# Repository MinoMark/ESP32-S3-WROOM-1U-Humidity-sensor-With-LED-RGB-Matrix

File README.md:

# ESP32-S3-WROOM-1U-Humidity-sensor-With-LED-RGB-Matrix
The project I am building is an ESP32-S3 WROOM-1U humidity sensor with an LED RGB matrix. This project is a really cool one. The ESP will control and read the data from the sensor and output certain colours, patterns, or make the lights move based on the temperature, humidity, and air quality.

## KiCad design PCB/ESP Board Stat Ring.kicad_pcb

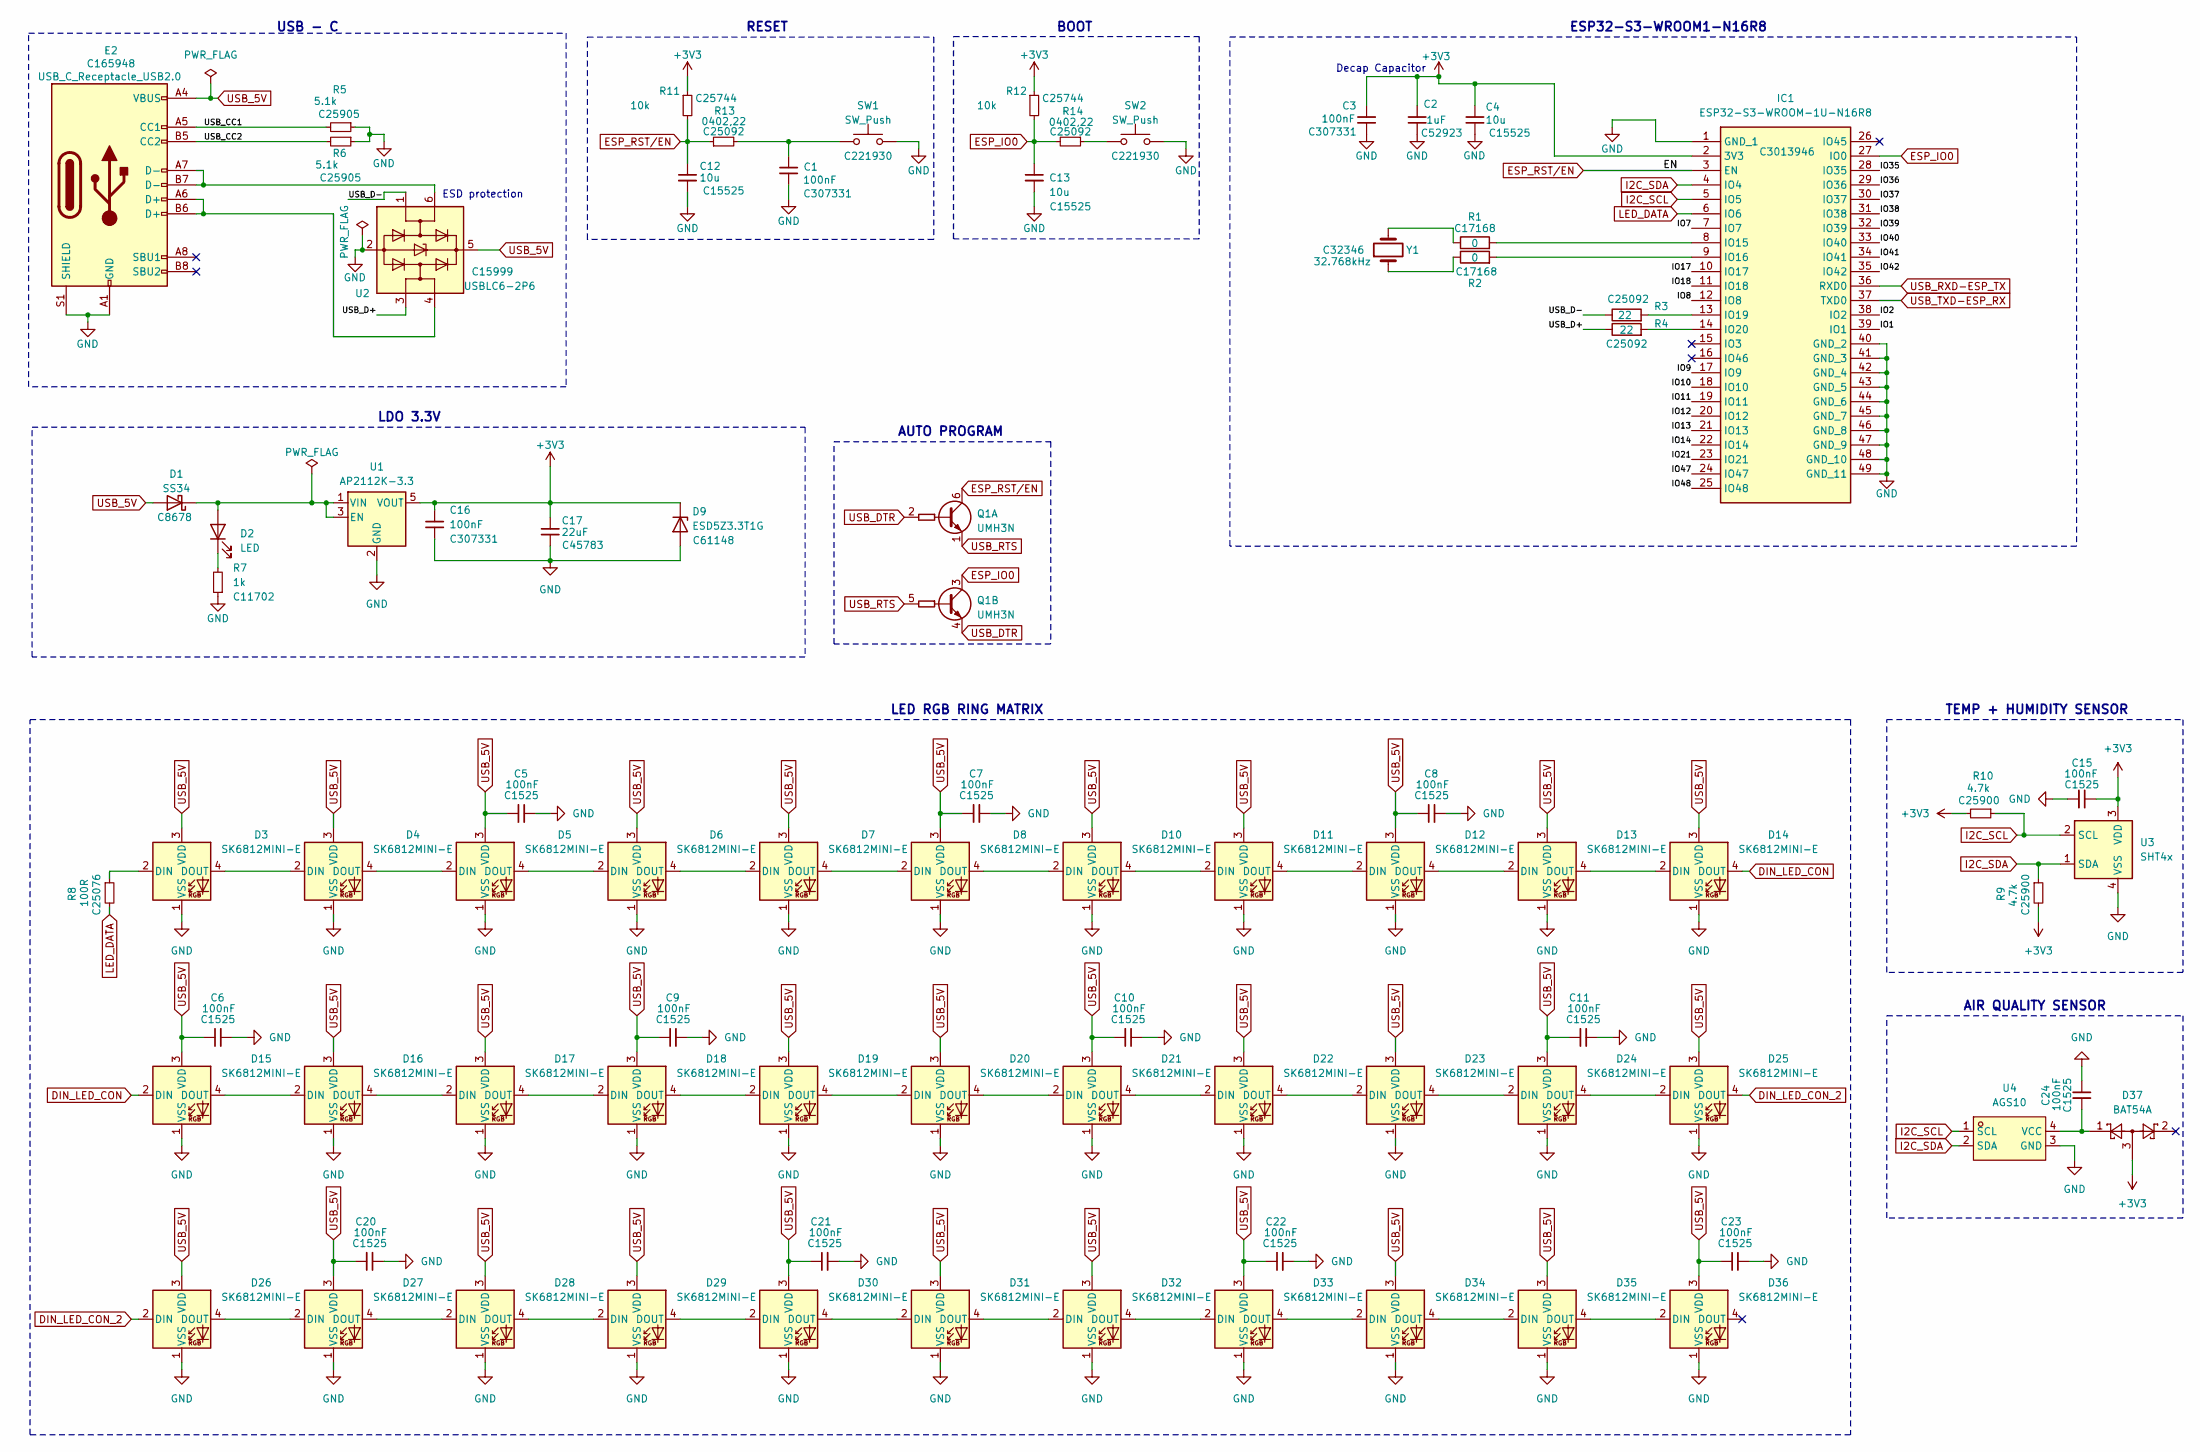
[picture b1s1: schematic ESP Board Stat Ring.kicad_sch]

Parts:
C1, C3, C16: 100nF; C_0402_1005Metric; MFGPN CL05B104KB54PNC; LCSC C307331
C2: 1uF; C_0402_1005Metric; MFGPN CL05A105KA5NQNC; LCSC C52923
C4: 10u; C_0402_1005Metric; MFGPN CL05B104KB54PNC; LCSC C15525
C5, C6, C7, C8, C9, C10, C11, C15, C20, C21, C22, C23, C24: 100nF; C_0402_1005Metric; MFGPN CL05B104KB54PNC; LCSC C1525
C12, C13: 10u; C_0402_1005Metric; MPN CL05A106MQ5NUNC; LCSC C15525
C17: 22uF; C_0805_2012Metric; MFGPN CL21A226MAQNNNE; LCSC C45783
D1: SS34; D_SMA; MPN SS34; LCSC C8678
D2: LED; LED_0603_1608Metric; MPN 19-217/GHC-YR1S2/3T; LCSC C72043
D3, D4, D5, D6, D7, D8, D10, D11, D12, D13, D14, D15, D16, D17, D18, D19, D20, D21, D22, D23, D24, D25, D26, D27, D28, D29, D30, D31, D32, D33, D34, D35, D36: SK6812MINI-E; LED_SK6812MINI-E_3.2x2.8mm_P1.5mm_ReverseMount; MPN SK6812MINI-E; LCSC C5149201
D9: ESD5Z3.3T1G; D_SOD-523; MPN ESD5Z3.3T1G; LCSC C61148
D37: BAT54A; SOT-23; MPN BAT54A; LCSC C181199
E2: USB_C_Receptacle_USB2.0; USB_C_Receptacle_HRO_TYPE-C-31-M-12; MPN TYPE-C-31-M-12; LCSC C165948
IC1: ESP32-S3-WROOM-1U-N16R8; ESP32-S3-WROOM-1U; Mouser Part Number 356-ESP32S3WM1UN16R8
Q1: UMH3N; SOT-363_SC-70-6; MPN UMH3N; LCSC C62892
R1, R2: 0; C_0402_1005Metric; MPN 0402WGF0000TCE; LCSC C17168
R3, R4: 22; C_0402_1005Metric; MPN 0402WGF220JTCE; LCSC C25092
R5, R6: 5.1k; R_0402_1005Metric; MFGPN 0402WGF5101TCE; LCSC C25905
R7: 1k; R_0402_1005Metric; MFGPN 0402WGF1002TCE; LCSC C11702
R8: 100R; R_0402_1005Metric; MFGPN 0402WGF5101TCE; LCSC C25076
R9, R10: 4.7k; R_0402_1005Metric; MFGPN 0402WGF5101TCE; LCSC C25900
R11, R12: 10k; R_0402_1005Metric; MFGPN 0402WGF1002TCE; LCSC C25744
R13, R14: 0402,22; R_0402_1005Metric; MFGPN 0402WGF220JTCE; LCSC C25092
SW1, SW2: SW_Push; SW_SPST_CK_RS282G05A3; MPN RS-282G05A3-SMRT; LCSC C221930
U1: AP2112K-3.3; SOT-23-5; MPN AP2112K-3.3TRG1; LCSC C51118
U2: USBLC6-2P6; SOT-666; MPN USBLC6-2P6; LCSC C15999
U3: SHT4x; Sensirion_DFN-4_1.5x1.5mm_P0.8mm_SHT4x_NoCentralPad; MPN SHT40-AD1F-R2; LCSC C54823945
U4: AGS10; SENSOR-SMD_AGS10; MPN AGS10; LCSC Part C3012632
Y1: 32.768kHz; Crystal_SMD_3215-2Pin_3.2x1.5mm; MPN 32.768kHz SMD3215; LCSC C32346

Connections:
+3V3: C2.1, C3.1, C4.1, C15.1, C16.1, C17.1, D9.1 (K), D37.3, IC1.2 (3V3), R9.2, R10.2, R11.1, R12.1, U1.5 (VOUT), U3.3 (VDD)
/IO1: IC1.39 (IO1)
/IO2: IC1.38 (IO2)
/IO7: IC1.7 (IO7)
/IO8: IC1.12 (IO8)
/IO9: IC1.17 (IO9)
/IO10: IC1.18 (IO10)
/IO11: IC1.19 (IO11)
/IO12: IC1.20 (IO12)
/IO13: IC1.21 (IO13)
/IO14: IC1.22 (IO14)
/IO17: IC1.10 (IO17)
/IO18: IC1.11 (IO18)
/IO21: IC1.23 (IO21)
/IO35: IC1.28 (IO35)
/IO36: IC1.29 (IO36)
/IO37: IC1.30 (IO37)
/IO38: IC1.31 (IO38)
/IO39: IC1.32 (IO39)
/IO40: IC1.33 (IO40)
/IO41: IC1.34 (IO41)
/IO42: IC1.35 (IO42)
/IO47: IC1.24 (IO47)
/IO48: IC1.25 (IO48)
/USB_CC1: E2.A5 (CC1), R5.2
/USB_CC2: E2.B5 (CC2), R6.2
/USB_D+: R4.1, U2.3 (I/O2)
/USB_D-: R3.1, U2.1 (I/O1)
DIN_LED_CON: D14.4 (DOUT), D15.2 (DIN)
DIN_LED_CON_2: D25.4 (DOUT), D26.2 (DIN)
ESP_IO0: C13.1, IC1.27 (IO0), Q1.3 (C2), R12.2, R14.2
ESP_RST/EN: C12.1, IC1.3 (EN), Q1.6 (C1), R11.2, R13.1
GND: C1.2, C2.2, C3.2, C4.2, C5.2, C6.2, C7.2, C8.2, C9.2, C10.2, C11.2, C12.2, C13.2, C15.2, C16.2, C17.2, C20.2, C21.2, C22.2, C23.2, C24.1, D3.1 (VSS), D4.1 (VSS), D5.1 (VSS), D6.1 (VSS), D7.1 (VSS), D8.1 (VSS), D9.2 (A), D10.1 (VSS), D11.1 (VSS), D12.1 (VSS), D13.1 (VSS), D14.1 (VSS), D15.1 (VSS), D16.1 (VSS), D17.1 (VSS), D18.1 (VSS), D19.1 (VSS), D20.1 (VSS), D21.1 (VSS), D22.1 (VSS), D23.1 (VSS), D24.1 (VSS), D25.1 (VSS), D26.1 (VSS), D27.1 (VSS), D28.1 (VSS), D29.1 (VSS), D30.1 (VSS), D31.1 (VSS), D32.1 (VSS), D33.1 (VSS), D34.1 (VSS), D35.1 (VSS), D36.1 (VSS), E2.A1 (GND), E2.A12 (GND), E2.B1 (GND), E2.B12 (GND), E2.S1 (SHIELD), IC1.1 (GND_1), IC1.40 (GND_2), IC1.41 (GND_3), IC1.42 (GND_4), IC1.43 (GND_5), IC1.44 (GND_6), IC1.45 (GND_7), IC1.46 (GND_8), IC1.47 (GND_9), IC1.48 (GND_10), IC1.49 (GND_11), R5.1, R6.1, R7.1, SW1.2, SW2.2, U1.2 (GND), U2.2 (GND), U3.4 (VSS), U4.3 (GND)
I2C_SCL: IC1.5 (IO5), R10.1, U3.2 (SCL), U4.1 (SCL)
I2C_SDA: IC1.4 (IO4), R9.1, U3.1 (SDA), U4.2 (SDA)
LED_DATA: IC1.6 (IO6), R8.2
unnamed: C1.1, R13.2, SW1.1
unnamed: D1.1 (K), D2.2 (A), U1.1 (VIN), U1.3 (EN)
unnamed: D2.1 (K), R7.2
unnamed: D3.2 (DIN), R8.1
unnamed: D3.4 (DOUT), D4.2 (DIN)
unnamed: D4.4 (DOUT), D5.2 (DIN)
unnamed: D5.4 (DOUT), D6.2 (DIN)
unnamed: D6.4 (DOUT), D7.2 (DIN)
unnamed: D7.4 (DOUT), D8.2 (DIN)
unnamed: D8.4 (DOUT), D10.2 (DIN)
unnamed: D10.4 (DOUT), D11.2 (DIN)
unnamed: D11.4 (DOUT), D12.2 (DIN)
unnamed: D12.4 (DOUT), D13.2 (DIN)
unnamed: D13.4 (DOUT), D14.2 (DIN)
unnamed: D15.4 (DOUT), D16.2 (DIN)
unnamed: D16.4 (DOUT), D17.2 (DIN)
unnamed: D17.4 (DOUT), D18.2 (DIN)
unnamed: D18.4 (DOUT), D19.2 (DIN)
unnamed: D19.4 (DOUT), D20.2 (DIN)
unnamed: D20.4 (DOUT), D21.2 (DIN)
unnamed: D21.4 (DOUT), D22.2 (DIN)
unnamed: D22.4 (DOUT), D23.2 (DIN)
unnamed: D23.4 (DOUT), D24.2 (DIN)
unnamed: D24.4 (DOUT), D25.2 (DIN)
unnamed: D26.4 (DOUT), D27.2 (DIN)
unnamed: D27.4 (DOUT), D28.2 (DIN)
unnamed: D28.4 (DOUT), D29.2 (DIN)
unnamed: D29.4 (DOUT), D30.2 (DIN)
unnamed: D30.4 (DOUT), D31.2 (DIN)
unnamed: D31.4 (DOUT), D32.2 (DIN)
unnamed: D32.4 (DOUT), D33.2 (DIN)
unnamed: D33.4 (DOUT), D34.2 (DIN)
unnamed: D34.4 (DOUT), D35.2 (DIN)
unnamed: D35.4 (DOUT), D36.2 (DIN)
unnamed: E2.A6 (D+), E2.B6 (D+), U2.4 (I/O2)
unnamed: E2.A7 (D-), E2.B7 (D-), U2.6 (I/O1)
unnamed: IC1.8 (IO15), R1.2
unnamed: IC1.9 (IO16), R2.2
unnamed: IC1.13 (IO19), R3.2
unnamed: IC1.14 (IO20), R4.2
unnamed: R1.1, Y1.2
unnamed: R2.1, Y1.1
unnamed: R14.1, SW2.1
unnamed: C24.2, D37.1, U4.4 (VCC)
USB_5V: C5.1, C6.1, C7.1, C8.1, C9.1, C10.1, C11.1, C20.1, C21.1, C22.1, C23.1, D1.2 (A), D3.3 (VDD), D4.3 (VDD), D5.3 (VDD), D6.3 (VDD), D7.3 (VDD), D8.3 (VDD), D10.3 (VDD), D11.3 (VDD), D12.3 (VDD), D13.3 (VDD), D14.3 (VDD), D15.3 (VDD), D16.3 (VDD), D17.3 (VDD), D18.3 (VDD), D19.3 (VDD), D20.3 (VDD), D21.3 (VDD), D22.3 (VDD), D23.3 (VDD), D24.3 (VDD), D25.3 (VDD), D26.3 (VDD), D27.3 (VDD), D28.3 (VDD), D29.3 (VDD), D30.3 (VDD), D31.3 (VDD), D32.3 (VDD), D33.3 (VDD), D34.3 (VDD), D35.3 (VDD), D36.3 (VDD), E2.A4 (VBUS), E2.A9 (VBUS), E2.B4 (VBUS), E2.B9 (VBUS), U2.5 (VBUS)
USB_DTR: Q1.2 (B1), Q1.4 (E2)
USB_RTS: Q1.1 (E1), Q1.5 (B2)
USB_RXD-ESP_TX: IC1.36 (RXD0)
USB_TXD-ESP_RX: IC1.37 (TXD0)

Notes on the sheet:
AUTO PROGRAM
USB - C
AIR QUALITY SENSOR
RESET
BOOT
LDO 3.3V
TEMP + HUMIDITY SENSOR
ESP32-S3-WROOM1-N16R8
LED RGB RING MATRIX
Decap Capacitor
ESD protection

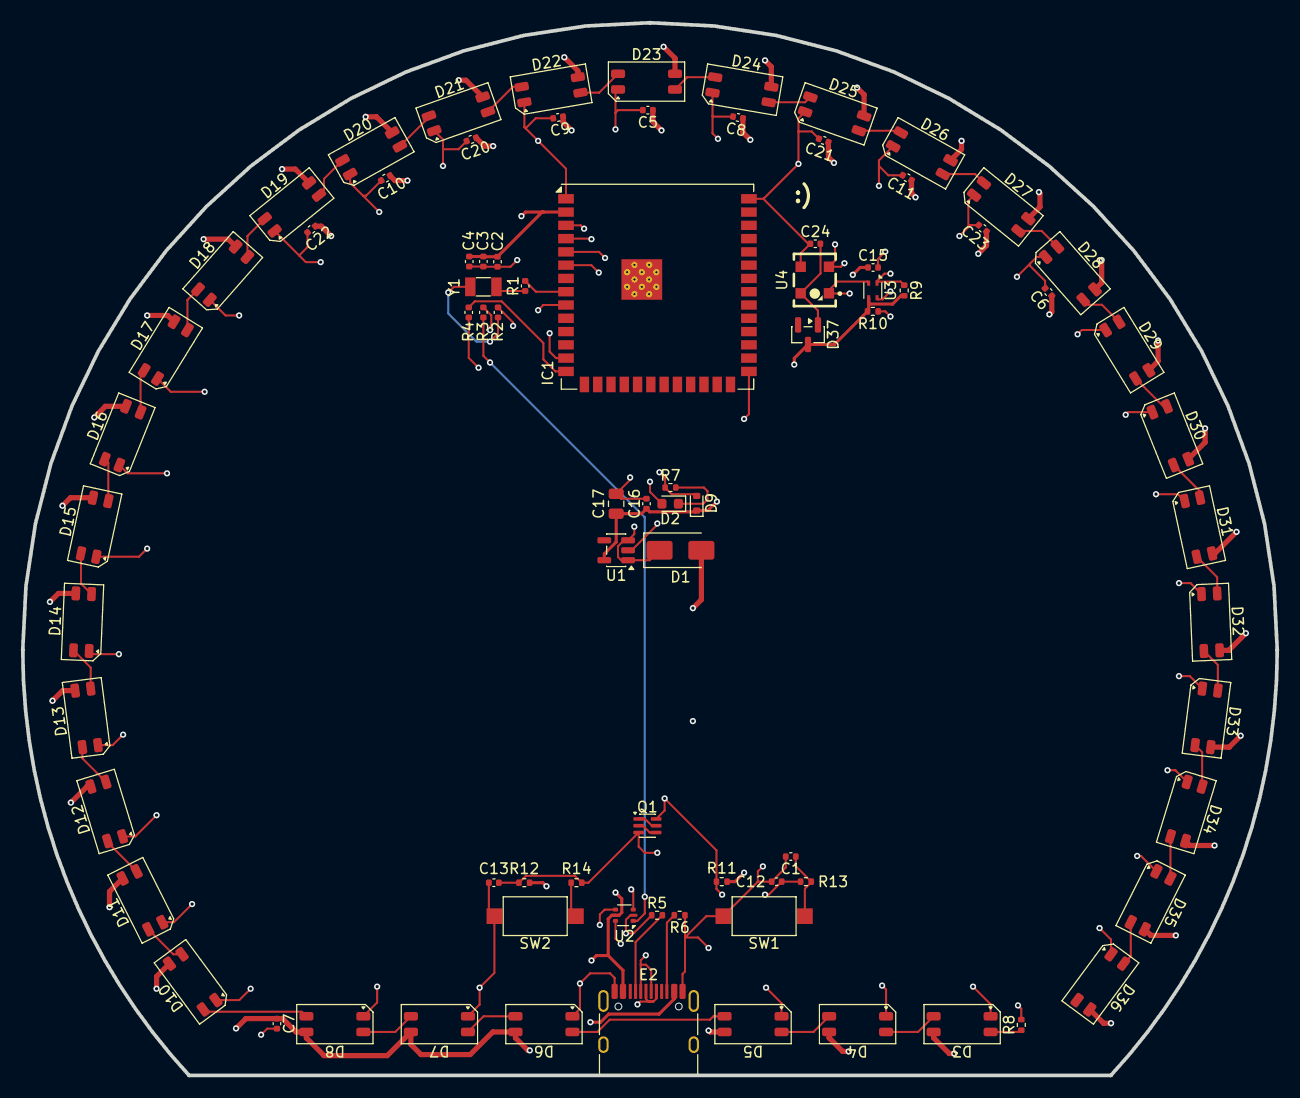
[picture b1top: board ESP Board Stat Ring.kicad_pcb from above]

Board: 4 copper layers, 120.0 x 100.7 mm, 82 parts (0 on the bottom side), 60 nets.
